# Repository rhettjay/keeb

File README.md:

# Custom Ergonomic Keyboards

- [neophyte](./neophyte/README.md)
- [neolexis](./neolexis/README.md)
- [tirosh](./tirosh/README.md)

## License
&copy; Rhett Bulkley
Released under the GNU General Public License, version 3 or later.

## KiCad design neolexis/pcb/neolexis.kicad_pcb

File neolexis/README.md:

# Checklist
## NEEDS TO HAVE
- [x] layout
- [x] thumb cluster
- [x] key placement
- [ ] pcb outline
- [ ] traces
- [ ] components
- [ ] "UC" placement (universal controller: pro micro nice_nano esp32)
- [ ] Bluetooth compat
- [ ] stl files
- [ ] key caps
- [ ] key cap legends

## NICE TO HAVE
- [ ] reversable pcb
- [ ] RGBLEDs
- [ ] OLED

## WONT HAVE BUT WANT
- [ ] IO expansion board w/ seed UC
- [ ] zig firmware

## TODO
- [ ] Add matrix diagram of keys

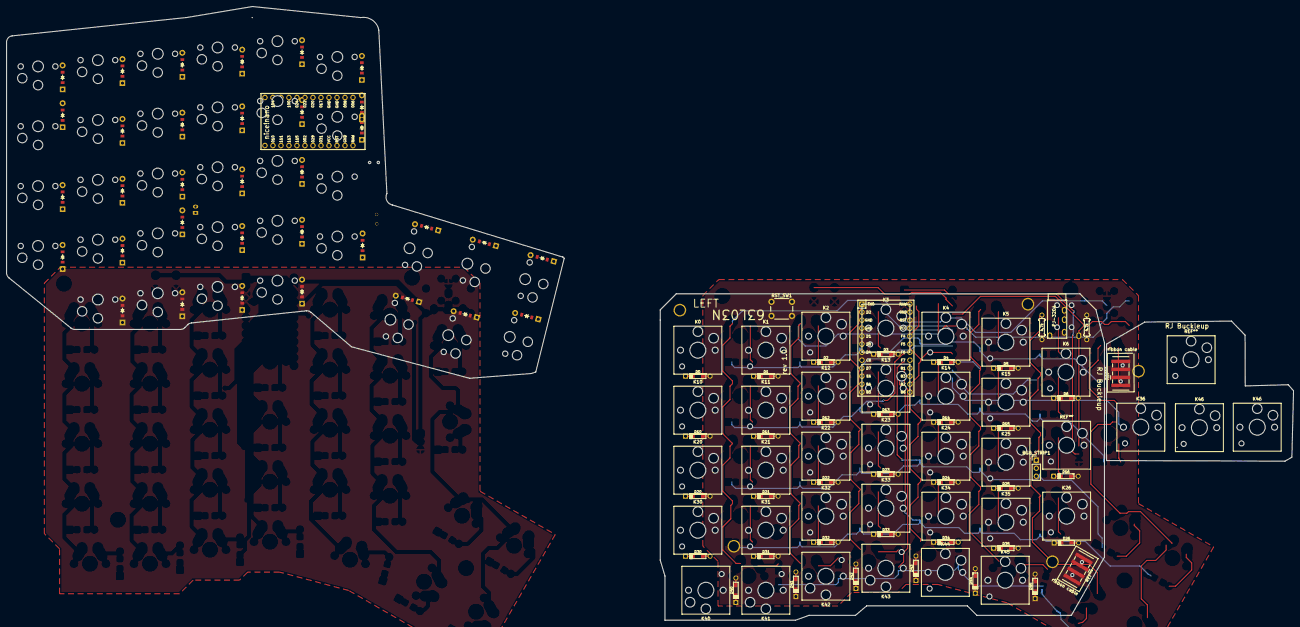
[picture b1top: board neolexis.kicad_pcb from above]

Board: 2 copper layers, 408.5 x 194.8 mm, 151 parts (0 on the bottom side), 50 nets.

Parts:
B1: Panasonic_EVQPUL_EVQPUC
D0, D1, D2#2, D3, D4, D5, D6#2, D10, D11, D12#2, D13, D14, D15#2, D16#2, D20#2, D21#2, D22#2, D23, D24, D25#2, D26#2, D30, D31#2, D32, D33, D34, D35, D40, D41, D42, D43, D44, D45: D; Diode-dual
D1#2, D2, D3#2, D4#2, D5#2, D6, D7, D8, D9, D10#2, D11#2, D12, D13#2, D14#2, D15, D16, D17, D18, D19, D20, D21, D22, D23#2, D24#2, D25, D26, D27, D28, D29, D30#2, D31, D32#2, D33#2, D34#2: ComboDiode
HOLE_M3, HOLE_M3#2, HOLE_M3#3, HOLE_M3#4, HOLE_M3#5: VAL**; HOLE_M3
JST1: JST_PH_S2B-PH-K_02x2.00mm_Angled
K0, K10, K20, K30: KEYSW; SW_Hotswap_Kailh_Choc_V1V2_1.25u
K1, K2, K3, K4, K5, K6, K11, K12, K13, K14, K15, K21, K22, K23, K24, K25, K26, K31, K32, K33, K34, K35, K40, K41, K42, K43, K44, K45: KEYSW; SW_Hotswap_Kailh_Choc_V1V2_1.00u
K36, K46, K46#2: KEYSW; SW_Hotswap_Kailh_Choc_V1V2_1.25u_90deg
MCU1: nice_nano
R1, R2: 4.7k; Resistor-Compact
RGB_STRIP1: Conn_01x03; Pin_Header_Straight_1x03_Pitch2.54mm
RST_SW1: SW_PUSH; SW_PUSH_6mm_h4.3mm
S1, S2, S3, S4, S5, S6, S7, S8, S9, S10, S11, S12, S13, S14, S15, S16, S17, S18, S19, S20, S21, S22, S23, S24, S25, S26, S27, S28, S29, S30, S31, S32, S33, S34: PG1350
T1: SPDT_C128955
TRRS1: Audio-Jack-4; TRRS-PJ-320A-dual
U1: ProMicro; ArduinoProMicro

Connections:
GND: RGB_STRIP1.3, RST_SW1.2, TRRS1.4, U1.3, U1.4, U1.23
unnamed: D0.2, K0.2
unnamed: D1.2, K1.2
unnamed: D2#2.2, K2.2
unnamed: D3.2, K3.2
unnamed: D4.2, K4.2
unnamed: D5.2, K5.2
unnamed: D6#2.2, K6.2
unnamed: D10.2, K10.2
unnamed: D11.2, K11.2
unnamed: D12#2.2, K12.2
unnamed: D13.2, K13.2
unnamed: D14.2, K14.2
unnamed: D15#2.2, K15.2
unnamed: D20#2.2, K20.2
unnamed: D21#2.2, K21.2
unnamed: D22#2.2, K22.2
unnamed: D23.2, K23.2
unnamed: D24.2, K24.2
unnamed: D25#2.2, K25.2
unnamed: D26#2.2, K26.2
unnamed: D30.2, K30.2
unnamed: D31#2.2, K31.2
unnamed: D32.2, K32.2
unnamed: D33.2, K33.2
unnamed: D34.2, K34.2
unnamed: D35.2, K35.2
unnamed: D40.2, K40.2
unnamed: D41.2, K41.2
unnamed: D42.2, K42.2
unnamed: D43.2, K43.2
unnamed: D44.2, K44.2
unnamed: D45.2, K45.2
RST: RST_SW1.1, U1.22
SCL: R2.1, TRRS1.2, U1.6
SDA: R1.1, TRRS1.3, U1.5
VCC: R1.2, R2.2, RGB_STRIP1.1, TRRS1.1, U1.21
col0: K0.1, K10.1, K20.1, K30.1, K40.1, U1.19
col1: K1.1, K11.1, K21.1, K31.1, K41.1, U1.18
col2: K2.1, K12.1, K22.1, K32.1, K42.1, U1.17
col3: K3.1, K13.1, K23.1, K33.1, K43.1, U1.16
col4: K4.1, K14.1, K24.1, K34.1, K44.1, U1.15
col5: K5.1, K15.1, K25.1, K35.1, K45.1, U1.14
col6: K6.1, K26.1, K36.1, K46.1, U1.13
rgb_data: RGB_STRIP1.2, U1.1
row0: D0.1, D1.1, D2#2.1, D3.1, D4.1, D5.1, D6#2.1, U1.7
row1: D10.1, D11.1, D12#2.1, D13.1, D14.1, D15#2.1, D16#2.1, U1.9
row2: D20#2.1, D21#2.1, D22#2.1, D23.1, D24.1, D25#2.1, D26#2.1, U1.10
row3: D30.1, D31#2.1, D32.1, D33.1, D34.1, D35.1, U1.11
row4: D40.1, D41.1, D42.1, D43.1, D44.1, D45.1, U1.12

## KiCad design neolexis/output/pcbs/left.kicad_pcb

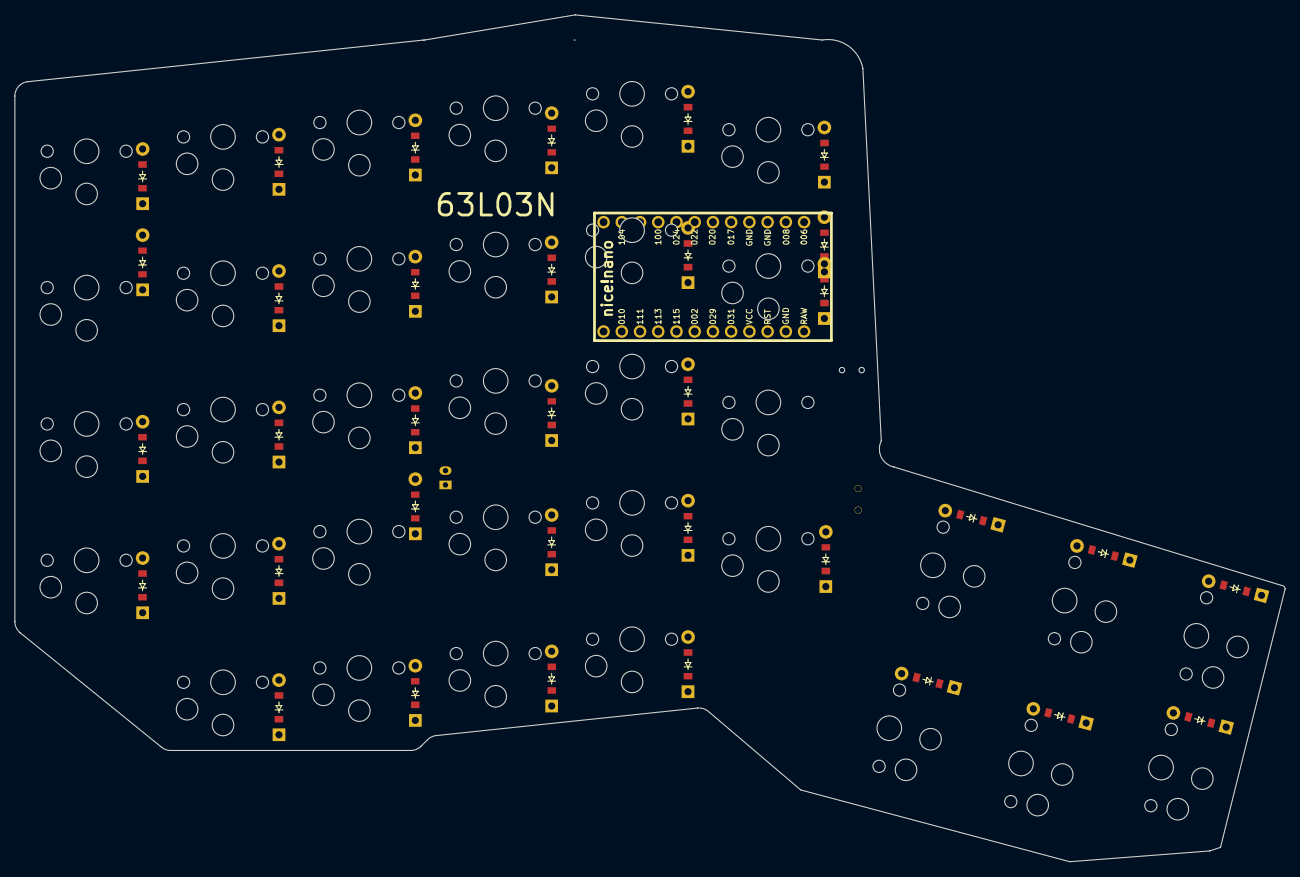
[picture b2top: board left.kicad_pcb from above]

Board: 2 copper layers, 177.0 x 118.0 mm, 72 parts (0 on the bottom side), 44 nets, no tracks yet.

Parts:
B1: Panasonic_EVQPUL_EVQPUC
D1, D2, D3, D4, D5, D6, D7, D8, D9, D10, D11, D12, D13, D14, D15, D16, D17, D18, D19, D20, D21, D22, D23, D24, D25, D26, D27, D28, D29, D30, D31, D32, D33, D34: ComboDiode
JST1: JST_PH_S2B-PH-K_02x2.00mm_Angled
MCU1: nice_nano
S1, S2, S3, S4, S5, S6, S7, S8, S9, S10, S11, S12, S13, S14, S15, S16, S17, S18, S19, S20, S21, S22, S23, S24, S25, S26, S27, S28, S29, S30, S31, S32, S33, S34: PG1350
T1: SPDT_C128955

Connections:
GND: B1.1, JST1.2, MCU1.3, MCU1.4, MCU1.23
P002: D2.1, D6.1, D10.1, D18.1, D33.1, MCU1.18
P009: D23.1, D26.1, MCU1.13
P010: D24.1, D27.1, MCU1.14
P029: D7.1, D11.1, D15.1, D19.1, D21.1, D31.1, MCU1.19
P031: D3.1, D8.1, D12.1, D20.1, D22.1, D29.1, D34.1, MCU1.20
P113: D4.1, D9.1, D13.1, D16.1, MCU1.16
P115: D1.1, D5.1, D14.1, D17.1, D25.1, D28.1, D30.1, D32.1, MCU1.17
RAW: MCU1.24, T1.2
RST: B1.2, MCU1.22
five_bottom: D16.2, S20.2
five_home: D17.2, S21.2
five_mod: D20.2, S24.2
five_num: D19.2, S23.2
five_top: D18.2, S22.2
four_bottom: D13.2, S15.2
four_home: D14.2, S16.2
four_mod: D34.2, S19.2
four_num: D15.2, S18.2
four_top: D33.2, S17.2
layer_bottom: D23.2, S29.2
layer_home: D24.2, S30.2
layer_in: D25.2, S31.2
one_home: D1.2, S1.2
one_mod: D3.2, S4.2
one_num: D31.2, S3.2
one_top: D2.2, S2.2
pos: JST1.1, T1.1
six_home: D30.2, S25.2
six_mod: D22.2, D29.2, S28.2
six_num: D21.2, S27.2
space_bottom: D26.2, S32.2
space_home: D27.2, S33.2
space_in: D28.2, S34.2
three_bottom: D9.2, S10.2
three_home: D32.2, S11.2
three_mod: D12.2, S14.2
three_num: D11.2, S13.2
three_top: D10.2, S12.2
two_bottom: D4.2, S5.2
two_home: D5.2, S6.2
two_mod: D8.2, S9.2
two_num: D7.2, S8.2
two_top: D6.2, S7.2

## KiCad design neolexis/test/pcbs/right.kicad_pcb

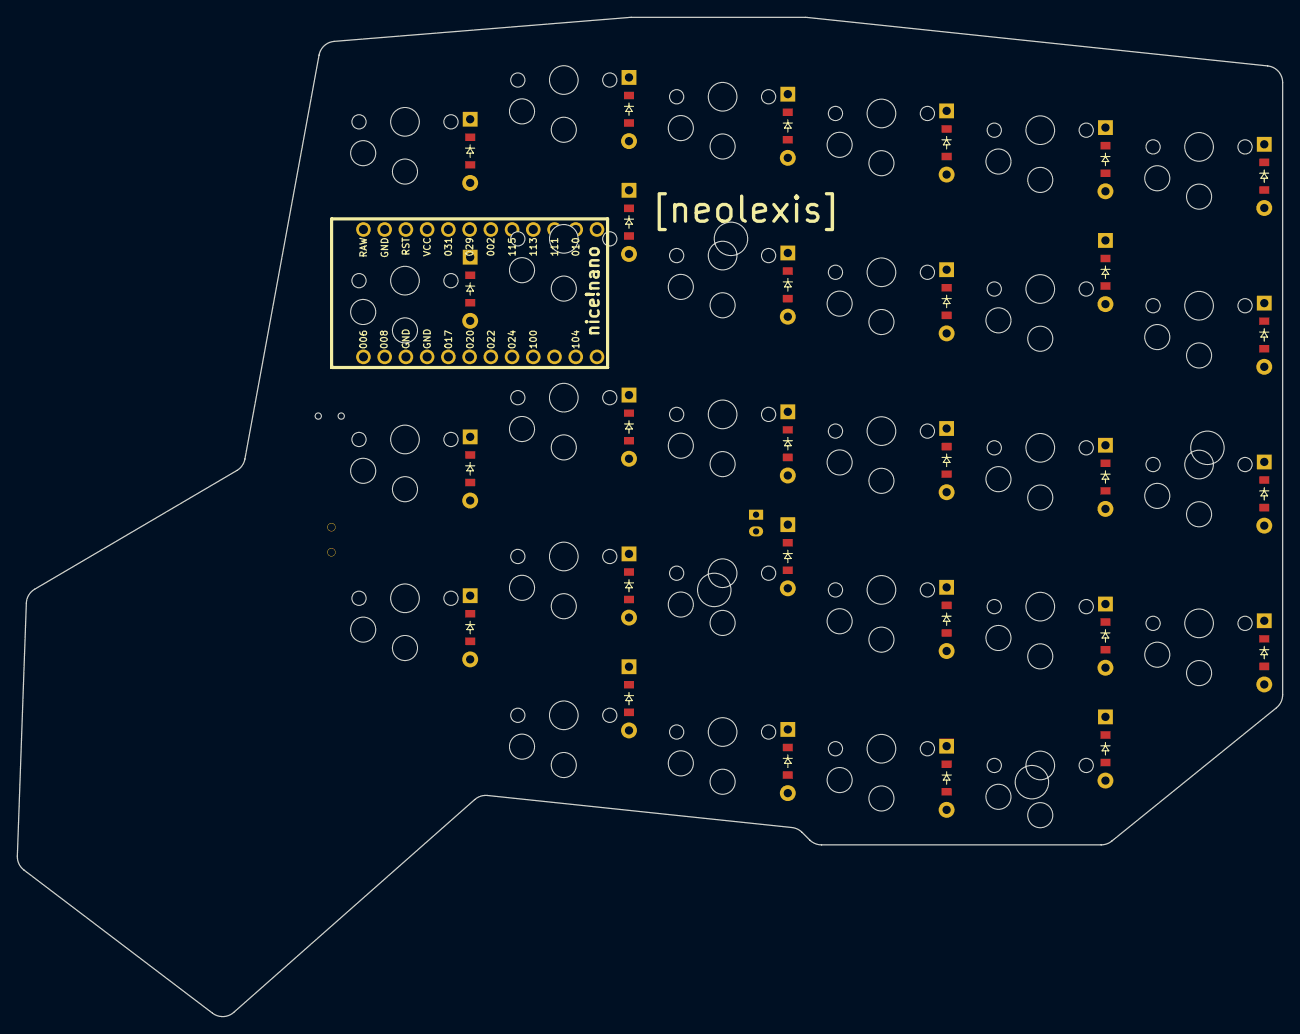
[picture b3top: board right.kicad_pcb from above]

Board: 2 copper layers, 151.4 x 119.5 mm, 60 parts (0 on the bottom side), 43 nets, no tracks yet.

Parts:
B1: Panasonic_EVQPUL_EVQPUC
D1, D2, D3, D4, D5, D6, D7, D8, D9, D10, D11, D12, D13, D14, D15, D16, D17, D18, D19, D20, D21, D22, D23, D24, D25, D26, D27, D28: ComboDiode
JST1: JST_PH_S2B-PH-K_02x2.00mm_Angled
MCU1: nice_nano
S1, S2, S3, S4, S5, S6, S7, S8, S9, S10, S11, S12, S13, S14, S15, S16, S17, S18, S19, S20, S21, S22, S23, S24, S25, S26, S27, S28: PG1350
T1: SPDT_C128955

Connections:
GND: B1.1, JST1.2, MCU1.3, MCU1.4, MCU1.23
P002: D2.1, D6.1, D10.1, D14.1, D18.1, D21.1, MCU1.18
P011: MCU1.10, S20.1, S21.1, S22.1, S23.1, S24.1
P017: MCU1.5, S25.1, S26.1, S27.1, S28.1
P020: MCU1.6, S1.1, S2.1, S3.1, S4.1
P022: MCU1.7, S5.1, S6.1, S7.1, S8.1, S9.1
P024: MCU1.8, S10.1, S11.1, S12.1, S13.1, S14.1
P029: D3.1, D11.1, D15.1, D24.1, D27.1, D28.1, MCU1.19
P031: D4.1, D7.1, D12.1, D16.1, D19.1, D22.1, MCU1.20
P100: MCU1.9, S15.1, S16.1, S17.1, S18.1, S19.1
P113: D8.1, D13.1, D23.1, D26.1, MCU1.16
P115: D1.1, D5.1, D9.1, D17.1, D20.1, D25.1, MCU1.17
RAW: MCU1.24, T1.2
RST: B1.2, MCU1.22
mirror_five_bottom: D26.2, S20.2
mirror_five_home: D17.2, S21.2
mirror_five_mod: D19.2, S24.2
mirror_five_num: D27.2, S23.2
mirror_five_top: D18.2, S22.2
mirror_four_bottom: D13.2, S15.2
mirror_four_home: D25.2, S16.2
mirror_four_mod: D16.2, S19.2
mirror_four_num: D15.2, S18.2
mirror_four_top: D14.2, S17.2
mirror_one_home: D1.2, S1.2
mirror_one_mod: D4.2, S4.2
mirror_one_num: D3.2, S3.2
mirror_one_top: D2.2, S2.2
mirror_six_home: D20.2, S25.2
mirror_six_mod: D22.2, S28.2
mirror_six_num: D28.2, S27.2
mirror_six_top: D21.2, S26.2
mirror_three_bottom: D8.2, S10.2
mirror_three_home: D9.2, S11.2
mirror_three_mod: D12.2, S14.2
mirror_three_num: D11.2, S13.2
mirror_three_top: D10.2, S12.2
mirror_two_bottom: D23.2, S5.2
mirror_two_home: D5.2, S6.2
mirror_two_mod: D7.2, S9.2
mirror_two_num: D24.2, S8.2
mirror_two_top: D6.2, S7.2
pos: JST1.1, T1.1

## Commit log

2024-08-07 feat: v0 keeb1
2024-08-07 feat: v0 outline
2024-08-08 feat: correction to raw dxf
2024-08-08 feat: key placement
2024-08-08 docs: add checklist
2024-08-08 chore: 63LO3N
2024-08-08 docs: organize CH405
2024-08-08 docs: blitzen
2024-08-08 docs: update readme
2024-08-08 docs: fix checklist
2024-08-08 chore: cleanup directory
2024-08-22 refactor: clean up padding
2024-08-23 fix: thumb cluster attempt
2024-08-26 fix: allow for any config
2024-08-26 feat: first workable iter
2024-08-26 chore: updates to version
2024-08-28 feat: consolidate
2024-08-29 feat: working sample
2024-08-29 refactor: move things around
2024-08-30 fix: adjust thumb layout
2024-09-03 fix: adjust thumb
2024-09-04 feat: neophye and tirosh
2024-09-08 feat: schematic first try
2024-09-11 feat: strict kicad sch
2024-09-11 fix: config corrections
2024-09-11 try schematic from base
2024-09-11 kicad
2024-09-14 feat: add new schematic
2024-09-14 fix: update ignore
2024-09-16 feat: import left
2024-09-25 feat: add reference
2024-10-03 feat: cluster outline
2024-10-03 chore: asset pngs
